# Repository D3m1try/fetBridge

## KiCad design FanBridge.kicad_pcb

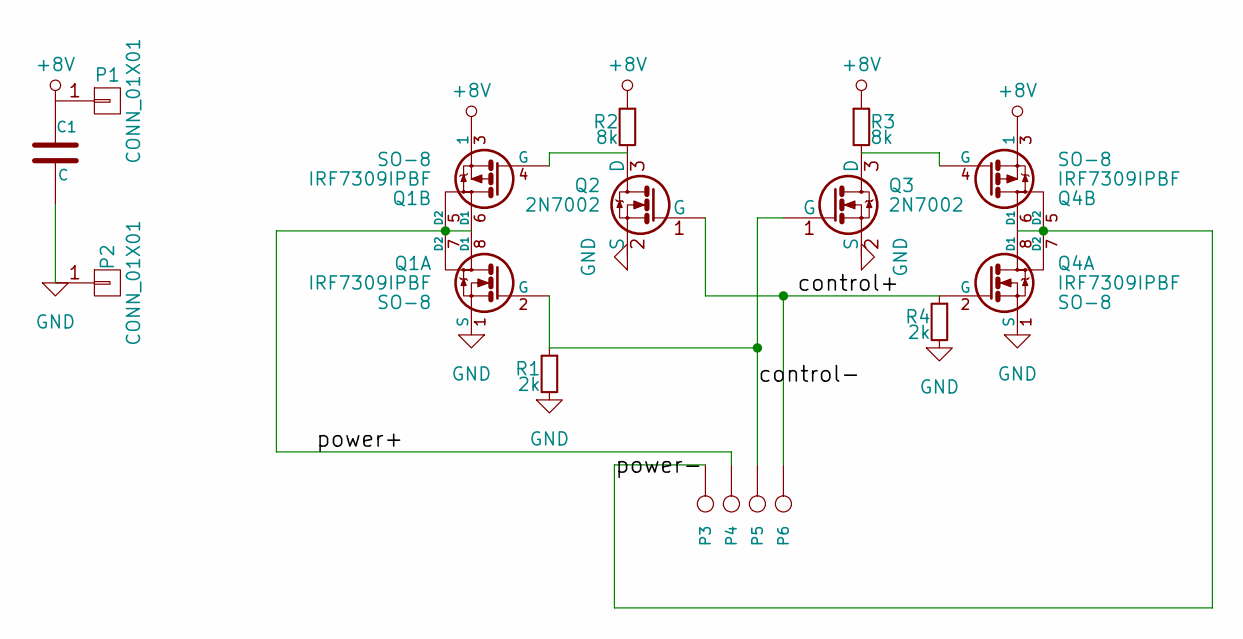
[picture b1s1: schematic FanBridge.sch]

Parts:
C1: C
P1, P2: CONN_01X01
P3, P4, P5, P6: CONN_1
Q1, Q4: IRF7309IPBF; SO-8
Q2, Q3: 2N7002; SOT-23
R1, R4: 2k
R2, R3: 8k

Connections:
+8V: C1.1, P1.1, Q1.3 (1), Q4.3 (1), R2.1, R3.1
/control+: P6.1, Q2.1 (G), Q4.2 (G), R4.1
/control-: P5.1, Q1.2 (G), Q3.1 (G), R1.1
/power+: P4.1, Q1.5 (D2), Q1.6 (D1), Q1.7 (D2), Q1.8 (D1)
/power-: P3.1, Q4.5 (D2), Q4.6 (D1), Q4.7 (D2), Q4.8 (D1)
GND: C1.2, P2.1, Q1.1 (S), Q2.2 (S), Q3.2 (S), Q4.1 (S), R1.2, R4.2
unnamed: Q3.3 (D), Q4.4 (G), R3.2
unnamed: Q1.4 (G), Q2.3 (D), R2.2

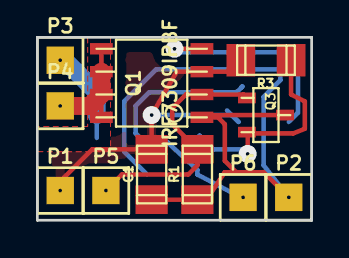
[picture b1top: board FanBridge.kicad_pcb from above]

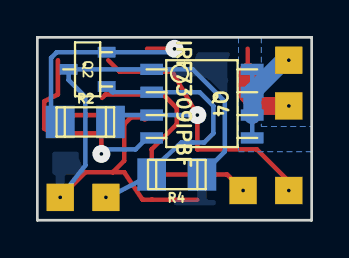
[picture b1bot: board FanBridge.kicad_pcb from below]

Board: 2 copper layers, 15.2 x 10.2 mm, 15 parts (4 on the bottom side), 8 nets.

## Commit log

2017-08-14 14082017
2017-08-15 15.08.2017
2017-08-17 17.08.2017
2017-08-18 18.08.2017
2017-08-21 21.08.2017
